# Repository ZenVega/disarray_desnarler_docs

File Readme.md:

# Macropad Collection

Open-hardware build documentation — KiCad projects, gerbers, bills of materials, laser-cut cases and artwork — for two custom macropads.

## The macropads

### [DisArray Desnarler](./disarray_desnarler/) &nbsp;→&nbsp; `disarray_desnarler/`

The original Schreibtischordnungsdienst macropad: a XIAO-RP2040 pad with hot-swap switches, an analog fader, and an optional rotary encoder, flashed with QMK. Includes the full build guide, laser-cut case, 3D-printed fader knob, sticker artwork, and the configuration instructions.

For a project overview, see [the Hackaday project page](https://hackaday.io/project/204536-disarray-desnarler).

### [macro_GOAT](./macro_GOAT/) &nbsp;→&nbsp; `macro_GOAT/`

An RP2040-Zero macropad with a 16-LED WS2812B array, hot-swap switches, and up to 4 optional EC11 rotary encoders. Includes the KiCad project, gerbers, SMD stencil, and the board artwork.

Both pads share the QMK firmware repository [ZenVega/qmk_disarray_desnarler](https://github.com/ZenVega/qmk_disarray_desnarler), which now holds keymaps for the Desnarler and the macro_GOAT.

## Repository layout

```
disarray_desnarler/      first macropad (build docs, PCB versions, case, configuration instructions)
macro_GOAT/              second macropad (PCB, gerbers, stencil, artwork)
instructions/            shared QMK flashing guide used by both boards
symbols_and_footprints/  shared KiCad symbol & footprint libraries used by both boards
```

> **KiCad note:** each project's `fp-lib-table` / `sym-lib-table` still contains machine-specific
> paths from the original authoring environment. The shared libraries now live at the repo root in
> [`symbols_and_footprints/`](./symbols_and_footprints/); re-point the library tables there when
> opening a project in KiCad.

## License

See [LICENSE](./LICENSE).

&mdash; _your Schreibtischordnungsdienst_

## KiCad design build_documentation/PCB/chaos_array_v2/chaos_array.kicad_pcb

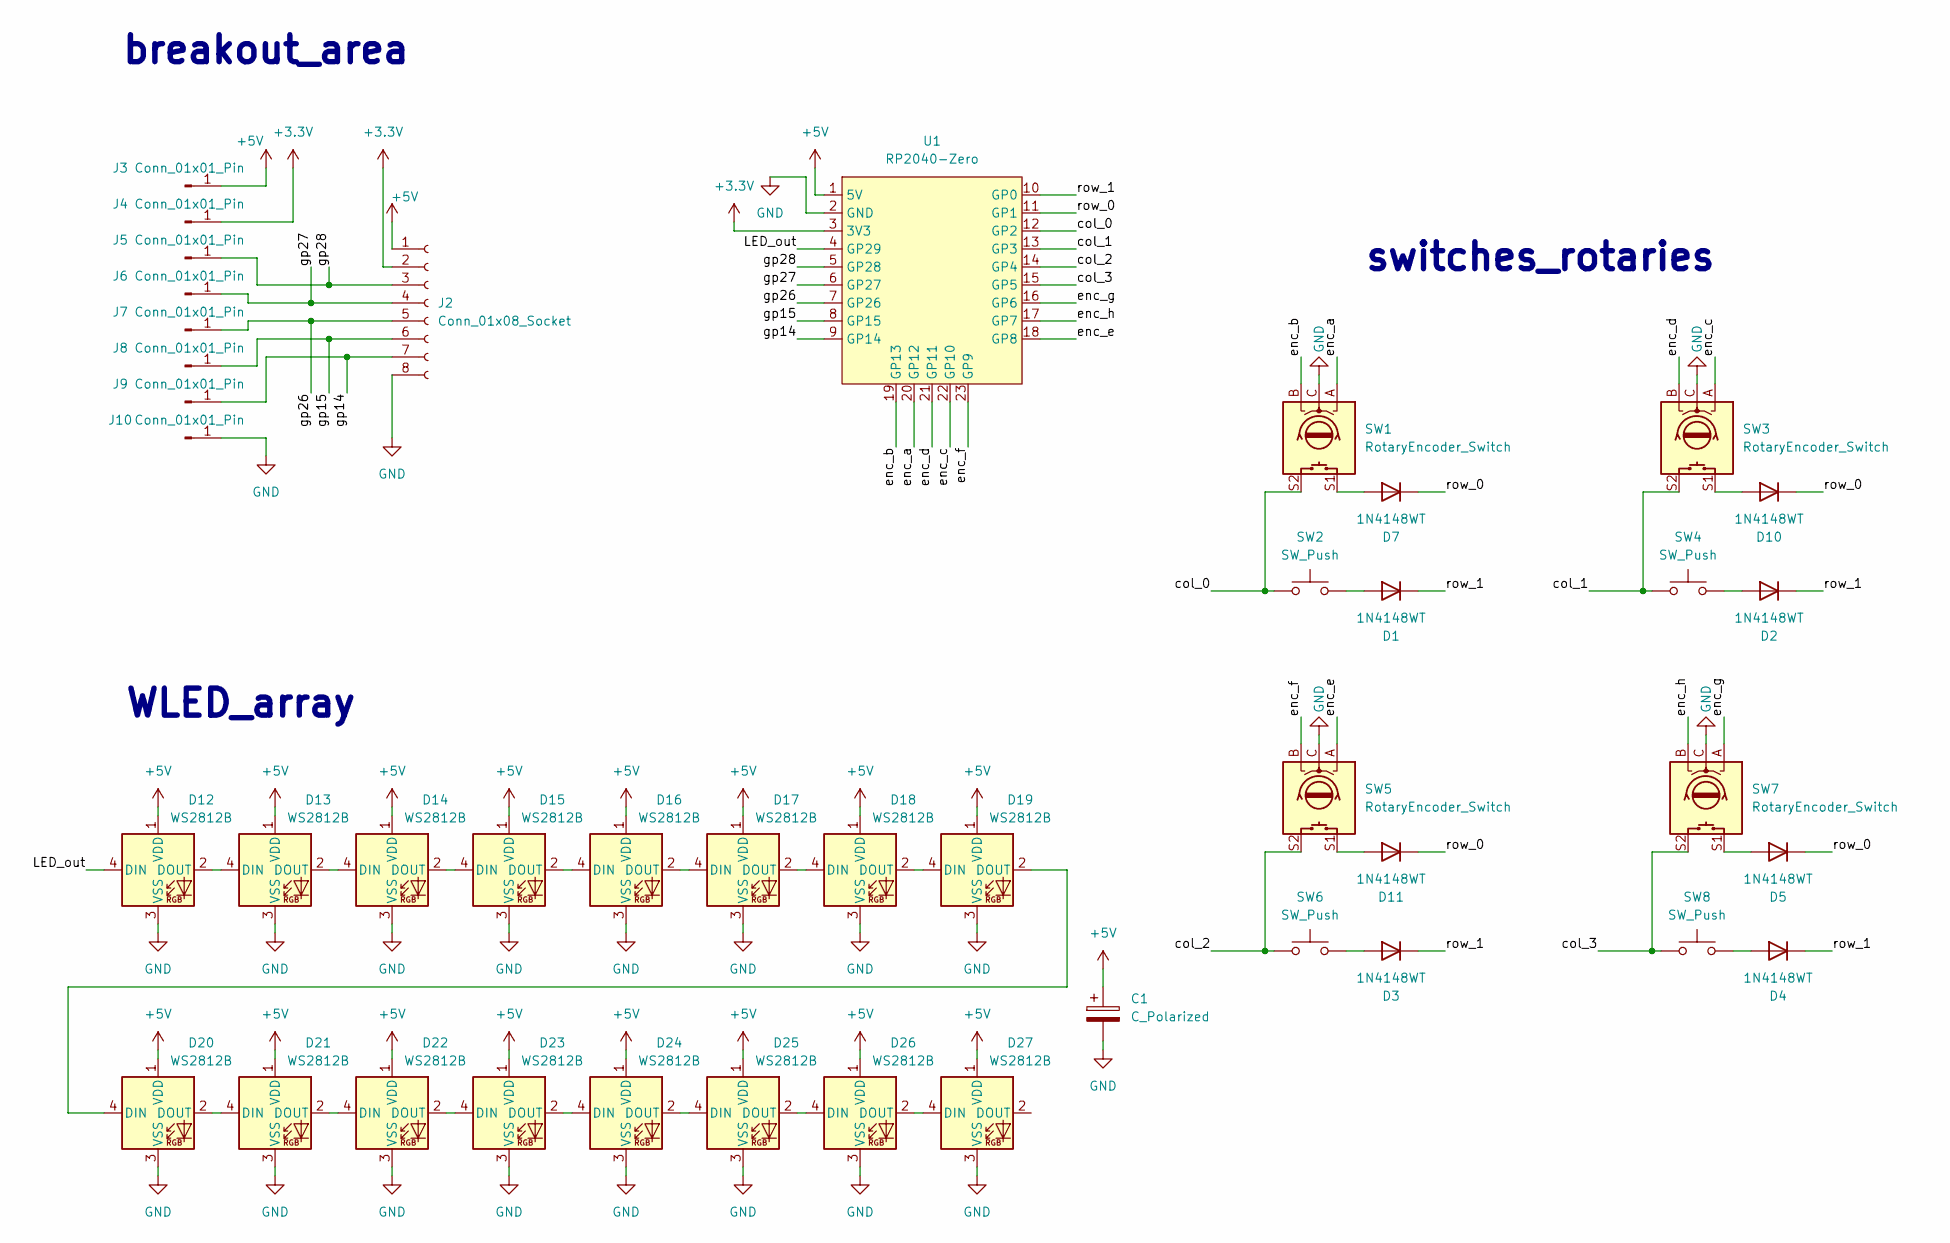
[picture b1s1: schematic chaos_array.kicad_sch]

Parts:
C1: C_Polarized; CP_Elec_6.3x5.8
D1, D2, D3, D4, D5, D7, D10, D11: 1N4148WT; D_MiniMELF
D12, D13, D14, D15, D16, D17, D18, D19, D20, D21, D22, D23, D24, D25, D26, D27: WS2812B; LED_WS2812B_PLCC4_5.0x5.0mm_P3.2mm
J2: Conn_01x08_Socket; JST_EH_B8B-EH-A_1x08_P2.50mm_Vertical
J3, J4, J5, J6, J7, J8, J9, J10: Conn_01x01_Pin; TestPoint_Pad_3.0x3.0mm
SW1, SW3, SW5, SW7: RotaryEncoder_Switch; Kailh_socket_MX_PG1350_EC11_optional
SW2, SW4, SW6, SW8: SW_Push; Kailh_socket_MX_PG1350_optional
U1: RP2040-Zero; RP2040 Zero

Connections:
+3.3V: J2.2, J4.1 (Pin_1_1), U1.3 (3V3)
+5V: C1.1, D12.1 (VDD), D13.1 (VDD), D14.1 (VDD), D15.1 (VDD), D16.1 (VDD), D17.1 (VDD), D18.1 (VDD), D19.1 (VDD), D20.1 (VDD), D21.1 (VDD), D22.1 (VDD), D23.1 (VDD), D24.1 (VDD), D25.1 (VDD), D26.1 (VDD), D27.1 (VDD), J2.1, J3.1 (Pin_1_1), U1.1 (5V)
/LED_out: D12.4 (DIN), U1.4 (GP29)
/col_0: SW1.S2, SW2.1, U1.12 (GP2)
/col_1: SW3.S2, SW4.1, U1.13 (GP3)
/col_2: SW5.S2, SW6.1, U1.14 (GP4)
/col_3: SW7.S2, SW8.1, U1.15 (GP5)
/enc_a: SW1.A, U1.20 (GP12)
/enc_b: SW1.B, U1.19 (GP13)
/enc_c: SW3.A, U1.22 (GP10)
/enc_d: SW3.B, U1.21 (GP11)
/enc_e: SW5.A, U1.18 (GP8)
/enc_f: SW5.B, U1.23 (GP9)
/enc_g: SW7.A, U1.16 (GP6)
/enc_h: SW7.B, U1.17 (GP7)
/gp14: J2.7, J9.1 (Pin_1_1), U1.9 (GP14)
/gp15: J2.6, J8.1 (Pin_1_1), U1.8 (GP15)
/gp26: J2.5, J7.1 (Pin_1_1), U1.7 (GP26)
/gp27: J2.4, J6.1 (Pin_1_1), U1.6 (GP27)
/gp28: J2.3, J5.1 (Pin_1_1), U1.5 (GP28)
/row_0: D5.1 (K), D7.1 (K), D10.1 (K), D11.1 (K), U1.11 (GP1)
/row_1: D1.1 (K), D2.1 (K), D3.1 (K), D4.1 (K), U1.10 (GP0)
GND: C1.2, D12.3 (VSS), D13.3 (VSS), D14.3 (VSS), D15.3 (VSS), D16.3 (VSS), D17.3 (VSS), D18.3 (VSS), D19.3 (VSS), D20.3 (VSS), D21.3 (VSS), D22.3 (VSS), D23.3 (VSS), D24.3 (VSS), D25.3 (VSS), D26.3 (VSS), D27.3 (VSS), J2.8, J10.1 (Pin_1_1), SW1.C, SW3.C, SW5.C, SW7.C, U1.2 (GND)
unnamed: D1.2 (A), SW2.2
unnamed: D2.2 (A), SW4.2
unnamed: D3.2 (A), SW6.2
unnamed: D4.2 (A), SW8.2
unnamed: D5.2 (A), SW7.S1
unnamed: D7.2 (A), SW1.S1
unnamed: D10.2 (A), SW3.S1
unnamed: D11.2 (A), SW5.S1
unnamed: D12.2 (DOUT), D13.4 (DIN)
unnamed: D13.2 (DOUT), D14.4 (DIN)
unnamed: D14.2 (DOUT), D15.4 (DIN)
unnamed: D15.2 (DOUT), D16.4 (DIN)
unnamed: D16.2 (DOUT), D17.4 (DIN)
unnamed: D17.2 (DOUT), D18.4 (DIN)
unnamed: D18.2 (DOUT), D19.4 (DIN)
unnamed: D19.2 (DOUT), D20.4 (DIN)
unnamed: D20.2 (DOUT), D21.4 (DIN)
unnamed: D21.2 (DOUT), D22.4 (DIN)
unnamed: D22.2 (DOUT), D23.4 (DIN)
unnamed: D23.2 (DOUT), D24.4 (DIN)
unnamed: D24.2 (DOUT), D25.4 (DIN)
unnamed: D25.2 (DOUT), D26.4 (DIN)
unnamed: D26.2 (DOUT), D27.4 (DIN)

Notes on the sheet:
switches_rotaries
WLED_array
breakout_area

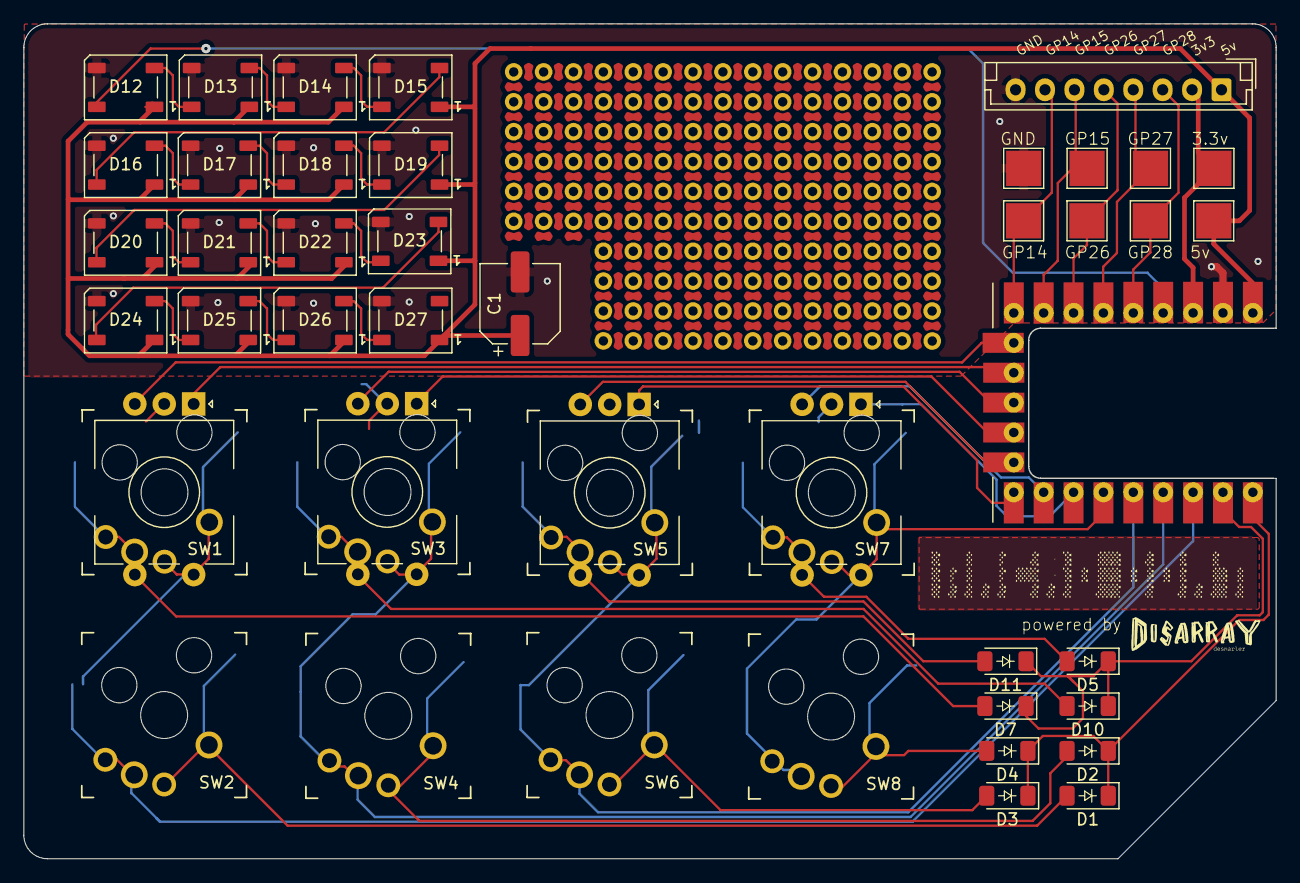
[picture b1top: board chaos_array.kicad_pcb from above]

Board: 2 copper layers, 106.4 x 70.9 mm, 43 parts (0 on the bottom side), 46 nets.

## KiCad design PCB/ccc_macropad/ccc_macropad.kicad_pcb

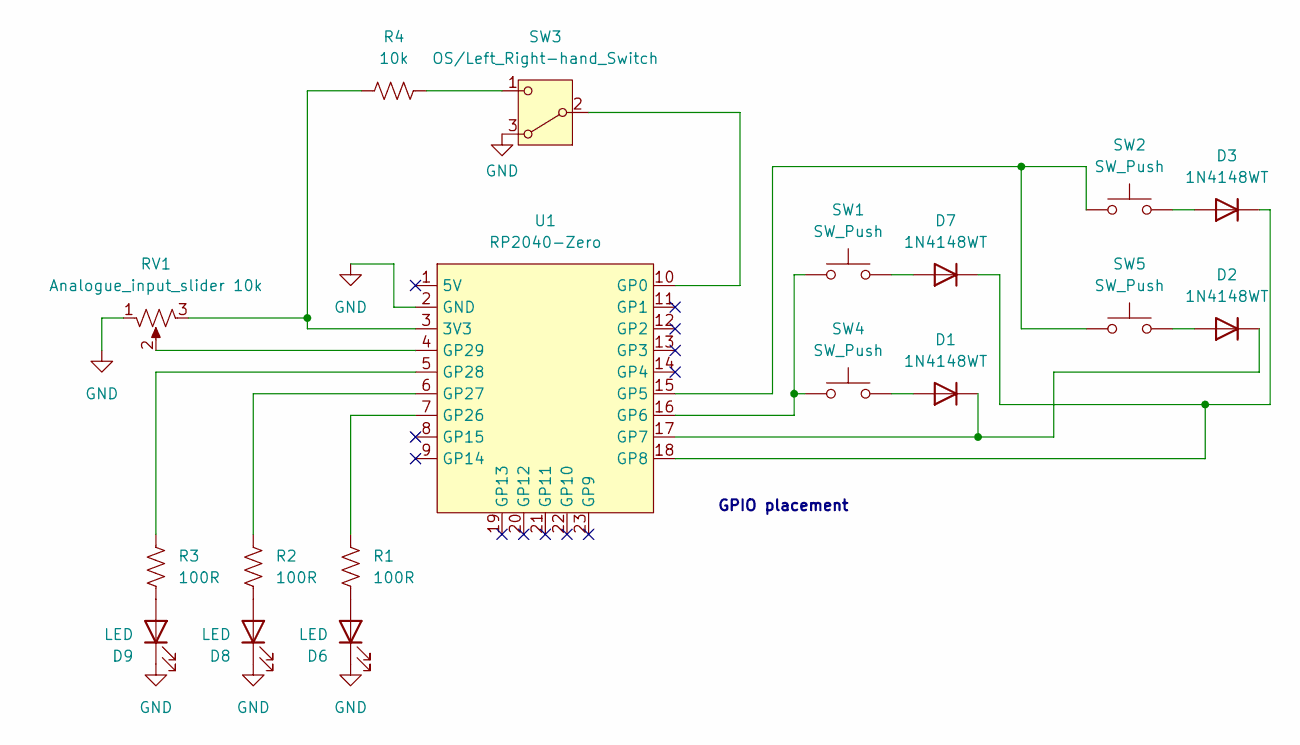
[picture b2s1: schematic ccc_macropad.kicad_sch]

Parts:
D1, D2, D3, D7: 1N4148WT; D_DO-35_SOD27_P5.08mm_Horizontal
D6, D8, D9: LED; LED_D3.0mm
R1, R2, R3: 100R; R_Axial_DIN0204_L3.6mm_D1.6mm_P5.08mm_Horizontal
R4: 10k; R_Axial_DIN0204_L3.6mm_D1.6mm_P5.08mm_Horizontal
RV1: Analogue_input_slider 10k; Potentiometer_slide_75mm_range_60mm_2_sets
SW1, SW2, SW4, SW5: SW_Push; Kailh_socket_MX_PG1350_optional
SW3: OS/Left_Right-hand_Switch; SPDT_3pin_2_pos_1P2T_tht_2.54mm_switch_sk12d07
U1: RP2040-Zero; RP2040 Zero

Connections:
GND: D6.1 (K), D8.1 (K), D9.1 (K), RV1.1, SW3.3 (A), U1.2 (GND); also elsewhere on the board
unnamed: D1.2 (A), SW4.2
unnamed: D1.1 (K), D2.1 (K), U1.17 (GP7)
unnamed: D2.2 (A), SW5.2
unnamed: D3.2 (A), SW2.2
unnamed: D3.1 (K), D7.1 (K), U1.18 (GP8)
unnamed: D6.2 (A), R1.1
unnamed: D7.2 (A), SW1.2
unnamed: D8.2 (A), R2.1
unnamed: D9.2 (A), R3.1
unnamed: SW3.2 (B), U1.10 (GP0)
unnamed: R4.1, SW3.1 (C)
unnamed: R4.2, RV1.3, U1.3 (3V3)
unnamed: SW2.1, SW5.1, U1.15 (GP5)
unnamed: SW1.1, SW4.1, U1.16 (GP6)
unnamed: R1.2, U1.7 (GP26)
unnamed: R2.2, U1.6 (GP27)
unnamed: R3.2, U1.5 (GP28)
unnamed 18: RV1.2, U1.4 (GP29); also elsewhere on the board

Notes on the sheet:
GPIO placement

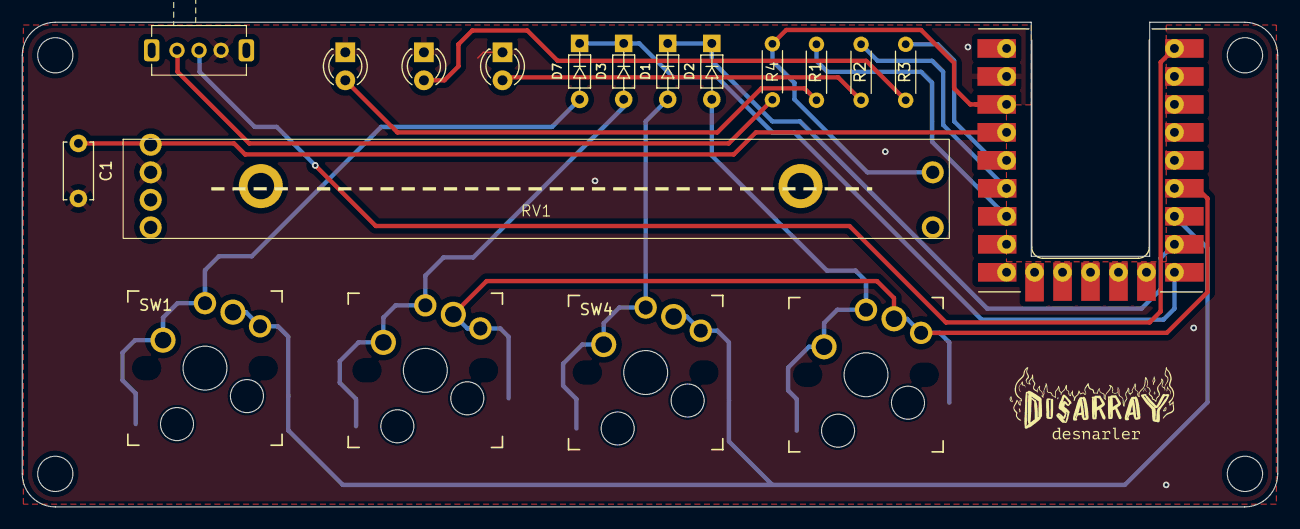
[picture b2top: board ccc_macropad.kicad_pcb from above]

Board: 2 copper layers, 114.0 x 44.0 mm, 19 parts (0 on the bottom side), 19 nets.

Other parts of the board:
C1: C; C_Disc_D5.0mm_W2.5mm_P5.00mm

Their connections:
GND: C1.2; also elsewhere on the board
unnamed 18: C1.1; also elsewhere on the board

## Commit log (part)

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2025-10-23 feat: update schematic to rp2040_zero
2025-10-23 PCB: feat add pinout table
2025-10-23 PCB: feat: new rp2040_zero footprint / rounded edges
2025-10-23 PCB:chores: cleanup schematic
2025-10-30 feat: cutout for MCU SMD mount
2025-10-30 added art to back: silkscreen and exposed copper
2025-10-30 logo added to front silkscreen
2025-10-31 fix: remove silkscreen of reference-switches/ reroute ground
2025-10-31 fixed missing V1, added svg files to art subdirectory
2025-10-31 fix: bigger traces/ more clearance
2025-11-07 feat: add assebly guide first draft // front and back panel laser svg
2025-11-08 first build diagram created. adding photos and scans for future use
2025-11-11 feat: add first draft assembly instructions
2025-11-14 fix:started redo on README
2025-11-14 feat: updated readme
2025-11-14 cleaned up build diagram files: deleted sketch, deleted directory with all the raw .heic photos and scans. deleted garbage .DS_Store file (a Mac thing). placed photoshop file in a hidden .photoshop_f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
2025-11-14 fix: updated Readme
2025-11-14 fix: add soldering pic
2025-11-19 new and improved diagram for the ReadMe
2025-11-20 feat: add buffer capacitor//increase board size// add foot holes
2025-11-20 refactoring: mini adjustments
2025-11-21 Add MIT License to the project
2025-11-21 documentation: add hackaday article to readme
2025-11-21 feat: add panes designs
2025-11-21 chores: duplicate PCBs for update to v1
2025-11-22 chores: proper versioning of art and PCBs
2025-11-23 documentation: small fixes/changes in Readme
2025-11-24 new silkscreen design for the front of v1.1
2025-11-24 chores: create updated gerbers
2025-11-24 feat: create gerbers
2025-11-24 refactoring: realign v1.1
2025-11-24 refactoring: remove merge monster
2025-11-24 chores: add to gitignore
2025-11-24 chores: remove version decimals
2025-11-30 git ignore edit -- added .DS_Store
2025-11-30 removed unnecessary leftover vector layers from svg files for the laser-cut case, greatly reducing file size
2025-11-30 removed old and unnecessary svg and dxf files
2025-11-30 restored missing silkscreen_front.svg, sorted case files into case_design directory
2025-12-01 PCB > ccc_macropad_v1.1 now contains up-to-date PCB files with art and PCBWay logo
2025-12-01 restored v1.1 PCB files, added new build diagram files
2025-12-01 rearranged art files into /PCB/PCB_vector_art, /logo, and /lasercut_case
2025-12-02 feat: created how_tos
2025-12-04 potential art for v1.1 case
2025-12-04 fix: picture how to flash
2025-12-04 fix: clean up
2025-12-09 fix: typos
2025-12-25 feat: V0 of more QMK doc
2025-12-25 fix: more qmk
2025-12-25 fix: insert image
2025-12-25 fix: optics
2025-12-26 Decumentation update: install guide
2025-12-26 feat: update soldering instructions
2025-12-26 fix: replace glitchy image
2025-12-27 fix: final re-read of Umlaut
2025-12-30 feat: add fader knob stl-file
2025-12-31 update docs
2026-01-31 docs: fix some typos and improve markdown formatting in readme
2026-04-22 fix(lasercut case design): add current case design, move old design files to separate directory
2026-04-24 chore(lasercut case): replace .ai files with .svg files
2026-04-30 How_to_flash.md: fix suggested command
    The correct "likely" command to flash is "flash" (not compile) and does
    not have the pure linux suffix.
2026-04-30 Docs: update dead links Because the file More_QMK.md was renamed to How_to_Umlaut.md update all links accordingly.
    fixes: 1c54fa2
2026-05-05 Add Kicad_Project v2.0
2026-05-05 Add footprints and symbols
2026-05-05 Add Link to WLED
2026-05-06 Create LED array and breakout area
2026-05-06 update BOM
2026-05-06 Update footprints
2026-05-06 basic layout PCB
2026-05-09 Routing
2026-05-15 reorganize folder structure
2026-05-15 feat(Readme): now includes Companion App and VimChaser references
2026-05-18 PCE reassemble switches
2026-05-18 Readme: typos and stylistic chagnes
